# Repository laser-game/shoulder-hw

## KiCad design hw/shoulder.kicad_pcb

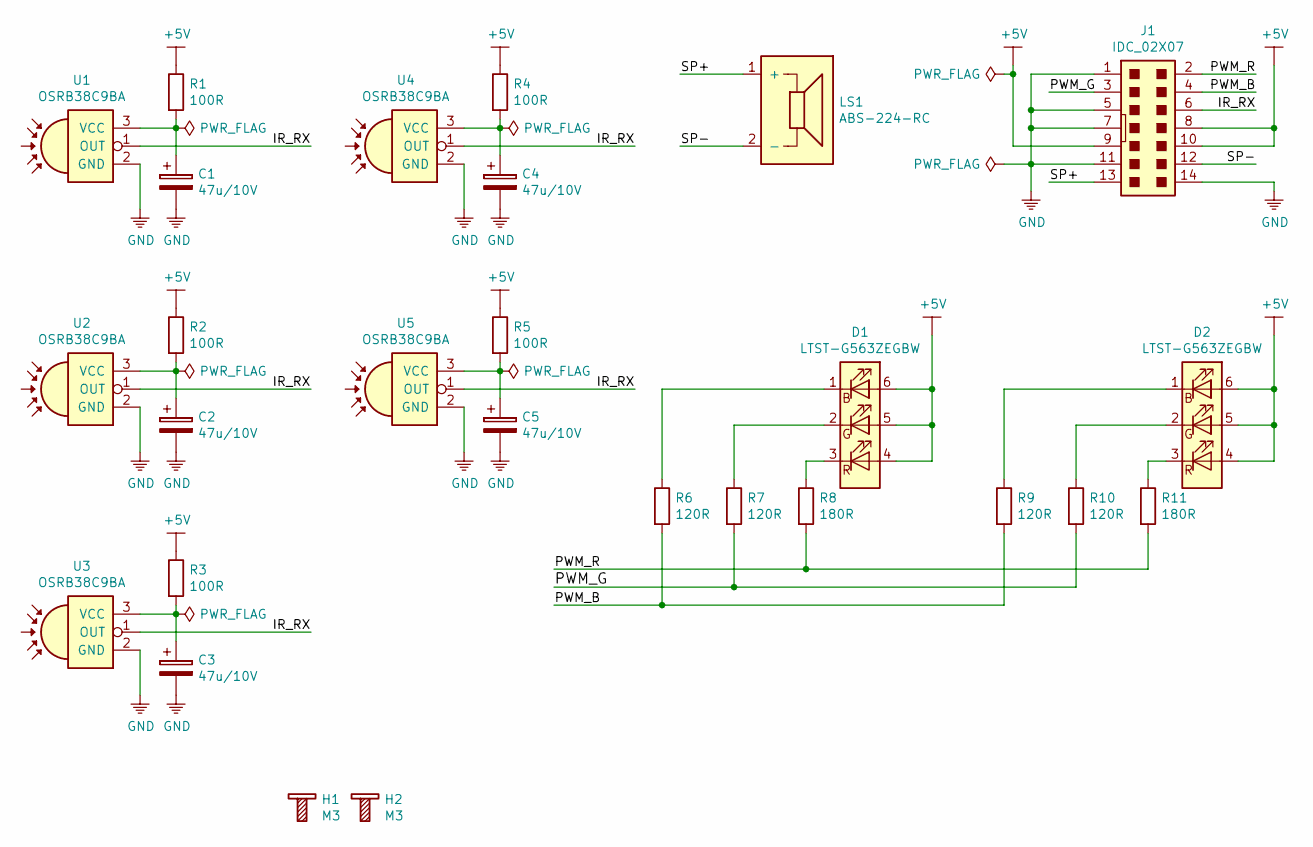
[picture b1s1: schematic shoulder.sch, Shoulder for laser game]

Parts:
C1, C2, C3, C4, C5: 47u/10V; CP_EIA-3528-21_Kemet-B
D1, D2: LTST-G563ZEGBW; LED_RGB_5050-6
H1, H2: M3; Bolt_M3
J1: IDC_02X07; IDC-Header_2x07_P2.54mm_Vertical
LS1: ABS-224-RC; REP-ABS-224-RC
R1, R2, R3, R4, R5: 100R; R_0805_2012Metric
R6, R7, R9, R10: 120R; R_0805_2012Metric
R8, R11: 180R; R_0805_2012Metric
U1, U2, U3, U4: OSRB38C9BA; OSRB8C9BA_Vertical
U5: OSRB38C9BA; OSRB8C9BA_Horizontal

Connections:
+5V: D1.4 (BA), D1.5 (GA), D1.6 (RA), D2.4 (BA), D2.5 (GA), D2.6 (RA), J1.8, J1.9, J1.10, R1.1, R2.1, R3.1, R4.1, R5.1
/IR_RX: J1.6, U1.1 (OUT), U2.1 (OUT), U3.1 (OUT), U4.1 (OUT), U5.1 (OUT)
/PWM_B: J1.4, R6.2, R9.2
/PWM_G: J1.3, R7.2, R10.2
/PWM_R: J1.2, R8.2, R11.2
/SP+: J1.13, LS1.1 (+)
/SP-: J1.12, LS1.2 (-)
GND: C1.2, C2.2, C3.2, C4.2, C5.2, J1.1, J1.5, J1.7, J1.11, J1.14, U1.2 (GND), U2.2 (GND), U3.2 (GND), U4.2 (GND), U5.2 (GND)
unnamed: C1.1, R1.2, U1.3 (VCC)
unnamed: C2.1, R2.2, U2.3 (VCC)
unnamed: C3.1, R3.2, U3.3 (VCC)
unnamed: C4.1, R4.2, U4.3 (VCC)
unnamed: C5.1, R5.2, U5.3 (VCC)
unnamed: D1.1 (RK), R6.1
unnamed: D1.2 (GK), R7.1
unnamed: D1.3 (BK), R8.1
unnamed: D2.1 (RK), R9.1
unnamed: D2.2 (GK), R10.1
unnamed: D2.3 (BK), R11.1

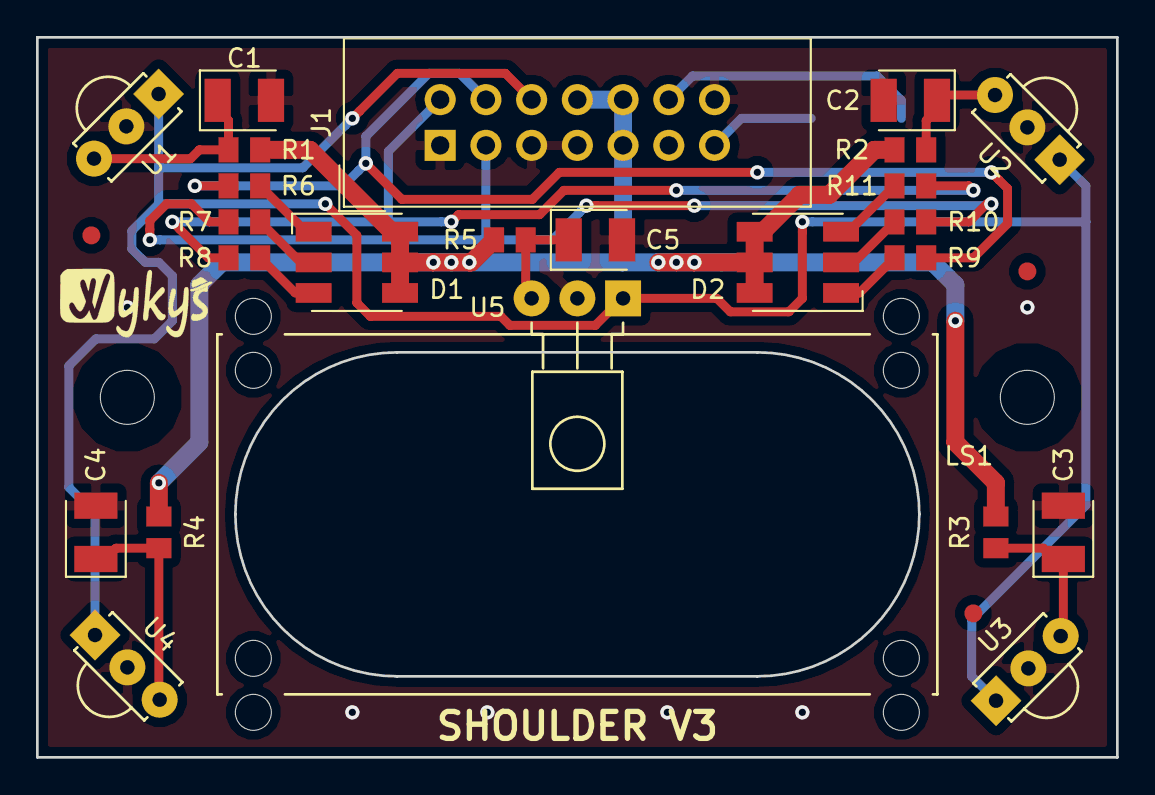
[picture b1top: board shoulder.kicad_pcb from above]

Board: 2 copper layers, 60.0 x 40.0 mm, 27 parts (0 on the bottom side), 19 nets.

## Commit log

2018-03-30 added license, gitignore and updated readme
2018-03-30 created kicad project
2018-03-30 updated schematic
2018-04-19 updated .gitignore
2018-04-19 added project.3dshapes
2018-04-19 update pcb placement compoents
2018-04-19 updated pcb
2018-04-19 updated pcb all nets conected
2018-05-02 added boom file and schematic for fabracation
2018-05-08 added placement files
